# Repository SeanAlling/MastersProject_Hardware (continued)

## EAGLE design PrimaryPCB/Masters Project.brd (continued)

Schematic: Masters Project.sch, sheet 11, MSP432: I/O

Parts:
LED12: GREEN; CHIPLED_0603; PARTNO LG R971-KN-1
R24, R25: 10K; R0603; PARTNO RMCF0805JT10K0
R27: 1K; R0603; PARTNO RC0805JR-071KL
TP22, TP23, TP24, TP26, TP27, TP28, TP29, TP30: TPB1,27; B1,27
U12: MSP432P401R; LQFP100; PARTNO MSP432P401RIPZR

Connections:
!RTC_INT1: U12.22 (P2.6/PM_TA0.3); also elsewhere on the board
!RTC_INT2: U12.24 (P10.4/TA3.0/C0.7); also elsewhere on the board
CHARGE_STATUS: U12.32 (P3.0/PM_UCA2STE); also elsewhere on the board
DISPLAY_D/!C: TP27.TP, U12.36 (P3.4/PM_UCB2STE); also elsewhere on the board
FPGA_DONE: U12.23 (P2.7/PM_TA0.4); also elsewhere on the board
FRAM_WP: U12.4 (P1.0/UCA0STE); also elsewhere on the board
INTERRUPT_OPT3001: U12.5 (P1.1/UCA0CLK); also elsewhere on the board
MCU_EN_CTL3: U12.19 (P2.3/PM_UCA1TXD/PM_UCA1SIMO); also elsewhere on the board
MCU_EN_CTL4: U12.18 (P2.2/PM_UCA1RXD/PM_UCA1SOMI); also elsewhere on the board
MCU_EN_CTL5: U12.39 (P3.7/PM_UCB2SOMI/PM_UCB2SCL); also elsewhere on the board
MCU_EN_CTL6: U12.20 (P2.4/PM_TA0.1); also elsewhere on the board
MCU_FPGA_2: U12.71 (P5.7/TA2.2/VREF-/VEREF-/C1.6); also elsewhere on the board
MCU_FPGA_3: U12.70 (P5.6/TA2.1/VREF+/VEREF+/C1.7); also elsewhere on the board
MCU_FPGA_4: U12.69 (P5.5/A0); also elsewhere on the board
MCU_FPGA_5: U12.68 (P5.4/A1); also elsewhere on the board
MCU_FPGA_6: U12.67 (P5.3/A2); also elsewhere on the board
MCU_FPGA_7: U12.66 (P5.2/A3); also elsewhere on the board
MCU_FPGA_8: U12.65 (P5.1/A4); also elsewhere on the board
MCU_FPGA_9: U12.64 (P5.0/A5); also elsewhere on the board
MCU_FPGA_10: U12.63 (P4.7/A6); also elsewhere on the board
MCU_FPGA_11: U12.62 (P4.6/A7); also elsewhere on the board
MCU_FPGA_12: U12.61 (P4.5/A8); also elsewhere on the board
MCU_FPGA_13: U12.60 (P4.4/HSMCLK/SVMHOUT/A9); also elsewhere on the board
MCU_FPGA_14: U12.59 (P4.3/MCLK/RTCCLK/A10); also elsewhere on the board
MCU_FPGA_15: U12.58 (P4.2/ACLK/TA2CLK/A11); also elsewhere on the board
MCU_SCL: R25.1, TP29.TP, U12.11 (P1.7/UCB0SOMI/UCB0SCL); also elsewhere on the board
MCU_SDA: R24.1, TP30.TP, U12.10 (P1.6/UCB0SIMO/UCB0SDA); also elsewhere on the board
MCU_SD_HDC1080: U12.17 (P2.1/PM_UCA1CLK); also elsewhere on the board
MCU_SD_OPT3001: U12.16 (P2.0/PM_UCA1STE); also elsewhere on the board
unnamed: R27.2, U12.9 (P1.5/UCB0CLK)
unnamed: LED12.C, R27.1
P10.5: U12.25 (P10.5/TA3.1/C0.6); also elsewhere on the board
RTC_CLKOUT: U12.21 (P2.5/PM_TA0.2); also elsewhere on the board
SPI_CLK: TP24.TP, U12.33 (P3.1/PM_UCA2CLK); also elsewhere on the board
SPI_CS_DISPLAY: TP28.TP, U12.37 (P3.5/PM_UCB2CLK); also elsewhere on the board
SPI_CS_FPGA: U12.38 (P3.6/PM_UCB2SIMO/PM_UCB2SDA); also elsewhere on the board
SPI_MISO: U12.34 (P3.2/PM_UCA2RXD/PM_UCA2SOMI)
SPI_MOSI: TP26.TP, U12.35 (P3.3/PM_UCA2TXD/PM_UCA2SIMO); also elsewhere on the board
UART_RX_XBEE: TP23.TP, U12.6 (P1.2/UCA0RXD/UCA0SOMI); also elsewhere on the board
UART_TX_XBEE: TP22.TP, U12.7 (P1.3/UCA0TXD/UCA0SIMO); also elsewhere on the board
VCC_MCU: LED12.A, R24.2, R25.2; also elsewhere on the board

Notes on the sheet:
TEST POINTS
INPUTS
COMMUNICATION
OUTPUTS
I/O

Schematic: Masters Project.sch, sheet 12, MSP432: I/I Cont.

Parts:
JP3: 2X5_HEADER1.27MM; CORTEX_DEBUG_10PIN
TP31, TP32: TPB1,27; B1,27
U12: MSP432P401R; LQFP100; PARTNO MSP432P401RIPZR

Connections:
!FLASH_HOLD: U12.75 (P9.3/TA3.4); also elsewhere on the board
!FLASH_WP: U12.80 (P6.6/TA2.3/UCB3SIMO/UCB3SDA/C1.1); also elsewhere on the board
EINK_!RST: TP31.TP, U12.46 (P8.2/TA3.2/A23); also elsewhere on the board
EINK_BUSY: TP32.TP, U12.47 (P8.3/TA3CLK/A22); also elsewhere on the board
GND: JP3.2, JP3.4; also elsewhere on the board
MCU_FPGA_1: U12.74 (P9.2/TA3.3); also elsewhere on the board
MCU_SPI_CLK: U12.77 (P6.3/UCB1CLK/C1.4); also elsewhere on the board
MCU_SPI_CS: U12.76 (P6.2/UCB1STE/C1.5); also elsewhere on the board
MCU_SPI_MISO: U12.79 (P6.5/UCB1SOMI/UCB1SCL/C1.2); also elsewhere on the board
MCU_SPI_MOSI: U12.78 (P6.4/UCB1SIMO/UCB1SDA/C1.3); also elsewhere on the board
P7.5: JP3.9, U12.27 (P7.5/PM_TA1.3/C0.4)
P7.6: JP3.7, U12.28 (P7.6/PM_TA1.2/C0.3)
P7.7: JP3.5, U12.29 (P7.7/PM_TA1.1/C0.2)
P8.0: JP3.3, U12.30 (P8.0/UCB3STE/TA1.0/C0.1)
P8.1: JP3.1, U12.31 (P8.1/UCB3CLK/TA2.0/C0.0)
P10.5: JP3.6; also elsewhere on the board
VCC_MCU: JP3.8, JP3.10; also elsewhere on the board
XBEE_RESET: U12.26 (P7.4/PM_TA1.4/C0.5); also elsewhere on the board

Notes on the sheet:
External Pin Connections
TEST POINTS
INPUTS
OUTPUTS
I/O
COMMUNICATION

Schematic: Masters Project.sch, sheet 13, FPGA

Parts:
C37, C38, C42, C43, C46, C47, C50, C51, C54, C55: 0.1uF; C0603; PARTNO 08055C104KAT2A
JP1, JP4: 2X5_HEADER1.27MM; CORTEX_DEBUG_10PIN
R30, R31, R32: 5k; R0603; PARTNO RC0805FR-075K1L
R35: 2k; R0603; PARTNO RC0805FR-072KL
U1: LCMXO2-640HC-4TG100C-NEW; QFP50P1600X1600X160-100N

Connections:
FPGA_DONE: U1.76 (PT11D/DONE); also elsewhere on the board
GND: C37.2, C38.2, C42.2, C43.2, C46.2, C47.2, C50.2, C51.2, C54.2, C55.2, JP1.10, JP4.8, R35.1, U1.6 (GND), U1.22 (GND), U1.33 (GND), U1.44 (GND), U1.56 (GND), U1.72 (GND), U1.79 (GND), U1.92 (GND); also elsewhere on the board
MCU_FPGA_1: U1.28 (PB4B); also elsewhere on the board
MCU_FPGA_2: U1.29 (PB4C); also elsewhere on the board
MCU_FPGA_3: U1.30 (PB4D); also elsewhere on the board
MCU_FPGA_4: U1.31 (PB6A/MCLK/CCLK); also elsewhere on the board
MCU_FPGA_5: U1.32 (PB6B/SO/SPISO); also elsewhere on the board
MCU_FPGA_6: U1.34 (PB6C/PCLKT2_0); also elsewhere on the board
MCU_FPGA_7: U1.35 (PB6D/PCLKC2_0); also elsewhere on the board
MCU_FPGA_8: U1.36 (PB10A); also elsewhere on the board
MCU_FPGA_9: U1.37 (PB10B); also elsewhere on the board
MCU_FPGA_10: U1.38 (PB10C/PCLKT2_1); also elsewhere on the board
MCU_FPGA_11: U1.39 (PB10D/PCLKC2_1); also elsewhere on the board
MCU_FPGA_12: U1.40 (PB12A); also elsewhere on the board
MCU_FPGA_13: U1.41 (PB12B); also elsewhere on the board
MCU_FPGA_14: U1.42 (PB12C); also elsewhere on the board
MCU_FPGA_15: U1.43 (PB12D); also elsewhere on the board
PT9A: JP1.8, U1.88 (PT9A/PCLKT0_1)
PT9B: JP1.6, U1.87 (PT9B/PCLKC0_1)
PT9C: JP1.4, U1.86 (PT9C/SCL/PCLKT0_0)
PT9D: JP1.2, U1.85 (PT9D/SDA/PCLKC0_0)
PT10A: JP1.3, U1.84 (PT10A)
PT10B: JP1.5, U1.83 (PT10B)
PT10C: JP1.7, U1.82 (PT10C/JTAGENB)
PT10D: JP1.9, U1.81 (PT10D/PROGRAMN)
SPI_CS_FPGA: U1.48 (PB14C/SN); also elsewhere on the board
TCK: JP4.6, R35.2, U1.91 (PT7C/TCK)
TDI: JP4.5, R31.1, U1.94 (PT7B/TDI)
TDO: JP4.7, R30.1, U1.95 (PT7A/TDO)
TMS: JP4.3, R32.1, U1.90 (PT7D/TMS)
VCC_FPGA: C37.1, C38.1, C42.1, C43.1, C46.1, C47.1, C50.1, C51.1, C54.1, C55.1, JP1.1, JP4.1, R30.2, R31.2, R32.2, U1.5 (VCCIO3), U1.23 (VCCIO3), U1.26 (VCCIO2), U1.46 (VCCIO2), U1.50 (VCC), U1.55 (VCCIO1), U1.73 (VCCIO1), U1.80 (VCCIO0), U1.93 (VCCIO0), U1.100 (VCC); also elsewhere on the board

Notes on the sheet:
Decoupling capacitors
JTAG Programmer
POWER
MCU-FPGA Connections
VCCIO1
VCCIO2
VCCIO3
VCCIO0
INPUTS
OUTPUTS
COMMUNICATION
I/O Connections
External Header
NOTE: Place close to indicated voltage pins.
UNUSED

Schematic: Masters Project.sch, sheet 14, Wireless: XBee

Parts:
C57: 47uF; C0603; PARTNO GRM21BR61A476ME15L
JP2: 1X3_HEADER; 1X3_FEMALE_HEADER_THROUGH_HOLE; PARTNO PRPC040SAAN-RC
JP26: XBEE-1B1; XBEE-1; PARTNO NPPN101BFCN-RC
LED14, LED15, LED18: GREEN; CHIPLED_0603; PARTNO LG R971-KN-1
LED16, LED17: GREEN; SML0805; PARTNO LG R971-KN-1
R37, R38, R39, R40, R41: 1K; R0603; PARTNO RC0805JR-071KL

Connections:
ASSOCIATE_LED: JP26.15 (DIO5), R39.1
GND: C57.2, JP26.10 (GND), LED16.C, LED17.C, LED18.C; also elsewhere on the board
unnamed: LED15.C, R38.2
unnamed: LED14.C, R37.2
unnamed: LED16.A, R39.2
unnamed: LED18.A, R41.2
unnamed: LED17.A, R40.2
RSSI: JP26.6 (RSSI), R41.1
STATUS_LED: JP26.13 (DIO9), R40.1
UART_RX_XBEE: JP26.2 (DOUT), R37.1; also elsewhere on the board
UART_TX_XBEE: JP26.3 (DIN), R38.1; also elsewhere on the board
VCC_XBEE: C57.1, JP26.1 (VDD), LED14.A, LED15.A; also elsewhere on the board
XBEE_CTS: JP2.2, JP26.12 (CTS)
XBEE_DTR: JP2.3, JP26.9 (DTR)
XBEE_RESET: JP26.5 (RESET); also elsewhere on the board
XBEE_RTS: JP2.1, JP26.16 (RTS)

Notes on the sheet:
NOTE: This module can be swapped for any module that is pn compattble with Xbee. For example the WiFi or RF modules by digi can be placed here.
NOTE: Minimum connections: VCC, GND, DOUT & DIN
NOTE: Do not populate for reduced current
Decoupling Capacitors
Status LED's
XBee
NOTE: Populate J2 only if XBee upgrades are needed
XBee Update
NOTE: Use to update software on XBee SOC
NOTE: Minimum connections for updating firmware: VCC, GND, DIN, DOUT, RTS & DTR
INPUTS
COMMUNICATION

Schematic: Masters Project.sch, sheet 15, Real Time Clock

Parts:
C68: 11mF; C1210K
Q9: ABS07-LR; 2-SMD
R3: 1K; R0603
TP40, TP41, TP42: TPB1,27; B1,27
U16: PCF8523; TSSOP14

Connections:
!RTC_INT1: TP40.TP, U16.13 (!INT1); also elsewhere on the board
!RTC_INT2: TP42.TP, U16.7 (!INT2); also elsewhere on the board
+BAT: R3.2, U16.4 (VBAT), U16.14 (VDD); also elsewhere on the board
GND: C68.2, U16.5 (VSS); also elsewhere on the board
MCU_SCL: U16.11 (SCL); also elsewhere on the board
MCU_SDA: U16.10 (SDA); also elsewhere on the board
unnamed: Q9.2, U16.1 (OSCI)
unnamed: Q9.1, U16.2 (OSCO)
RTC_CLKOUT: TP41.TP, U16.8 (CLKOUT); also elsewhere on the board
RTC_VCAP: C68.1, R3.1

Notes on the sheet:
SuperCap
NOTE: Resistor used to provide current limiting to the capacitor. Larger resistor = longer RC time constant = longer time to charge
Real Time Clock
NOTE: At ambiant temperature the average supply is 150nA. The maximum supply current is 3.6uA.
TEST POINTS
INPUTS
COMMUNICATION
OUTPUTS

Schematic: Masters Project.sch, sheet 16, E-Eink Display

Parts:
C1, C2, C36, C39, C40, C41, C44, C45, C48, C49, C52: 1uF; C0603
D1, D3, D4: SCHOTTKY; SOD3716X128
L2: 100uH; LPS3015
Q3: MOSFET-NCH; SOT95P237X112-3
R1: 0.47; R0603
R2: 100k; R0603
U18: 4.2-E-INK-DISPLAY; FPC-24PIN-0.5MM

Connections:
DISPLAY_D/!C: U18.11 (D/!C); also elsewhere on the board
EINK_!RST: U18.10 (!RST); also elsewhere on the board
EINK_BUSY: U18.9 (BUSY); also elsewhere on the board
GDR: Q3.1 (G), R2.2, U18.2 (GDR)
GND: C1.2, C2.2, C36.2, C39.2, C40.2, C41.2, C44.2, C45.2, C48.2, C49.2, D4.2 (C), R1.1, R2.1, U18.8 (BS1), U18.17 (VSS); also elsewhere on the board
PREVGH: C48.1, D1.2 (C), U18.21 (PREVGH)
PREVGL: C49.1, D3.1 (A), U18.23 (PREVGL)
RESE: Q3.2 (S), R1.2, U18.3 (RESE)
SPI_CLK: U18.13 (D0(SCK)); also elsewhere on the board
SPI_CS_DISPLAY: U18.12 (!CS); also elsewhere on the board
SPI_MOSI: U18.14 (D1(MOSI)); also elsewhere on the board
SW: C52.1, D1.1 (A), L2.1, Q3.3 (D)
SWGL: C52.2, D3.2 (C), D4.1 (A)
VCC_DISPLAY: C41.1, L2.2, U18.15 (VDDIO), U18.16 (VCI); also elsewhere on the board
VCOM: C40.1, U18.24 (VCOM)
VDD: C1.1, U18.18 (VDD)
VGH: C45.1, U18.5 (VGH)
VGL: C44.1, U18.4 (VGL)
VPP: C2.1, U18.19 (VPP)
VSH: C36.1, U18.20 (VSH)
VSL: C39.1, U18.22 (VSL)

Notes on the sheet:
RATED >= 25V
RATED>= 50V
RATED >=50V
Power Converter
INPUTS
COMMUNICATION
OUTPUTS

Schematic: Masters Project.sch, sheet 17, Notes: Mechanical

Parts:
FD1, FD2, FD3, FD4, FD5, FD6, FD7, FD8: FIDUCIAL1X2; FIDUCIAL-1X2
H1, H2, H3, H4: STAND-OFF

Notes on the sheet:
Fiducial One per corner, top and bottom
Mounting Hole One per corner
BOTTOM
TOP
GND
Stackup

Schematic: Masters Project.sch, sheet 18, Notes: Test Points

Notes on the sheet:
TP1: +BAT TP2: GND TP3: VCC_USB TP4: VCC_HDC1080 TP5: VCC_OPT3001 TP6: VCC_FPGA TP7: VCC_XBEE TP8: VCC_MEMORY TP9: VCC_DISPLAY TP10: VCC_MCU TP11: GND TP12: GND TP13: GND TP14: GND TP15: GND TP16: GND TP17: GND TP18: GND TP19: !RST TP20: N$139
TP21: N$131 TP22: UART_TX_XBEE TP23: UART_RX_XBEE TP24: SPI_CLK TP25: CHARGE_STATUS TP26: SPI_MOSI TP27: DISPLAY_D/!C TP28: SPI_CS_DISPLAY TP29: MCU_SCL TP30: MCU_SDA TP31: EINK_!RST TP32: EINK_BUSY TP33: !FLASH_WP TP34: FRAM_WP TP35: !FLASH_HOLD TP36: MCU_SPI_MISO TP37: MCU_SPI_CS TP38: MCU_SPI_CL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

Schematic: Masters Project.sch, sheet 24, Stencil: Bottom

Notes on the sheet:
N/A

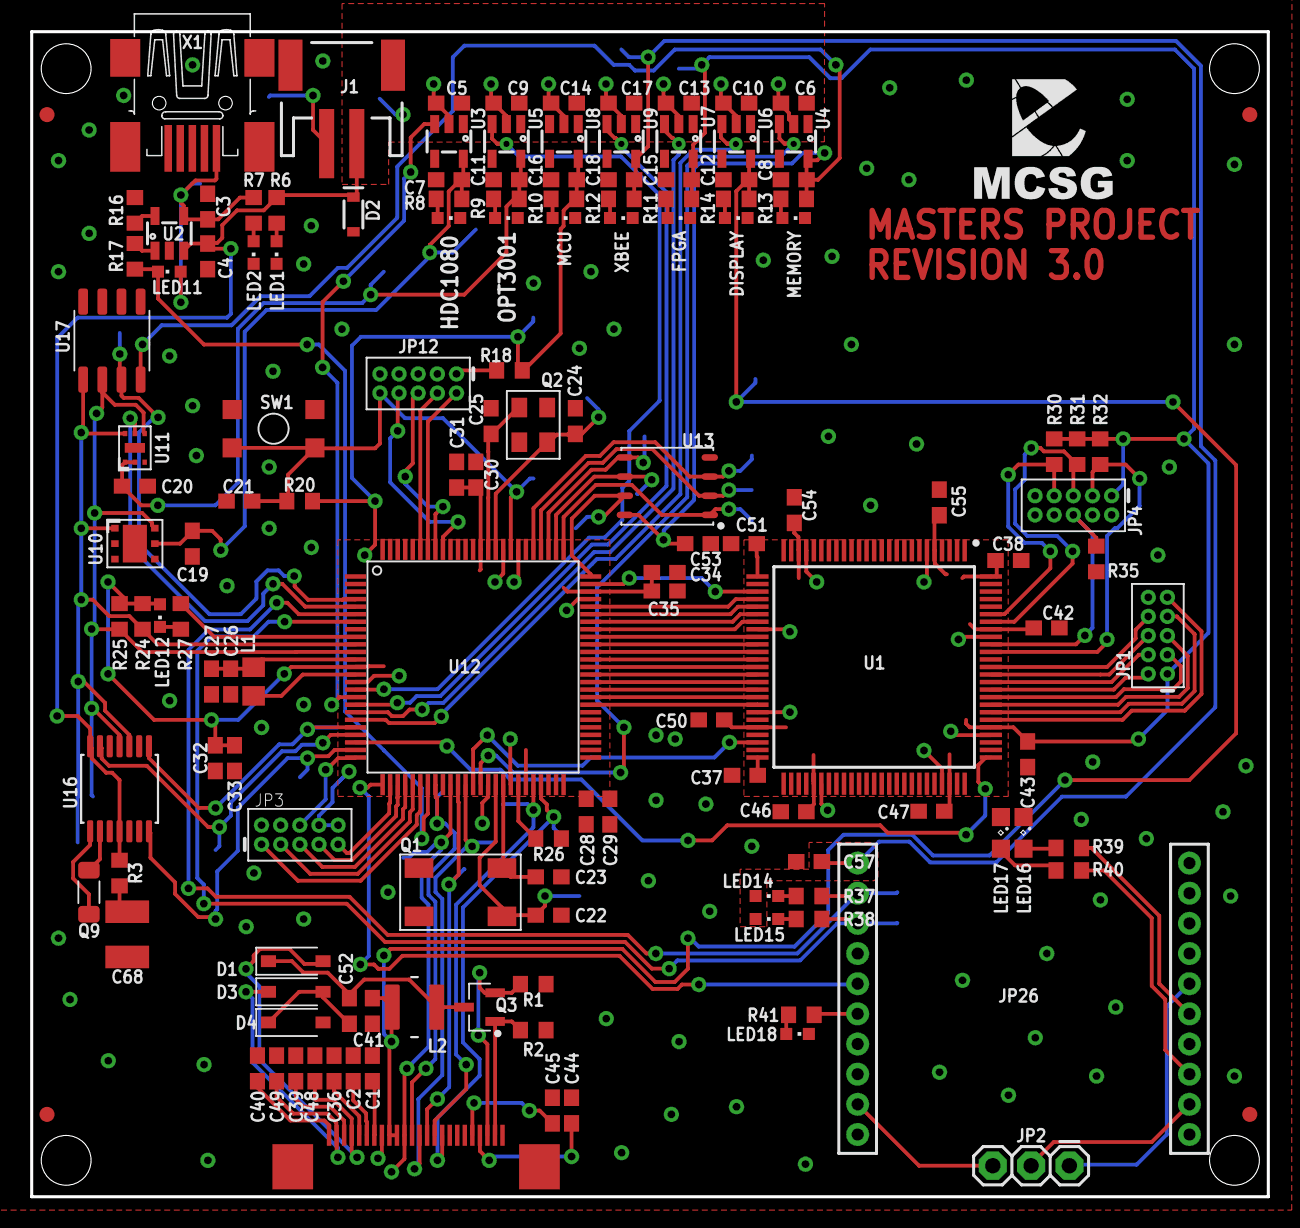
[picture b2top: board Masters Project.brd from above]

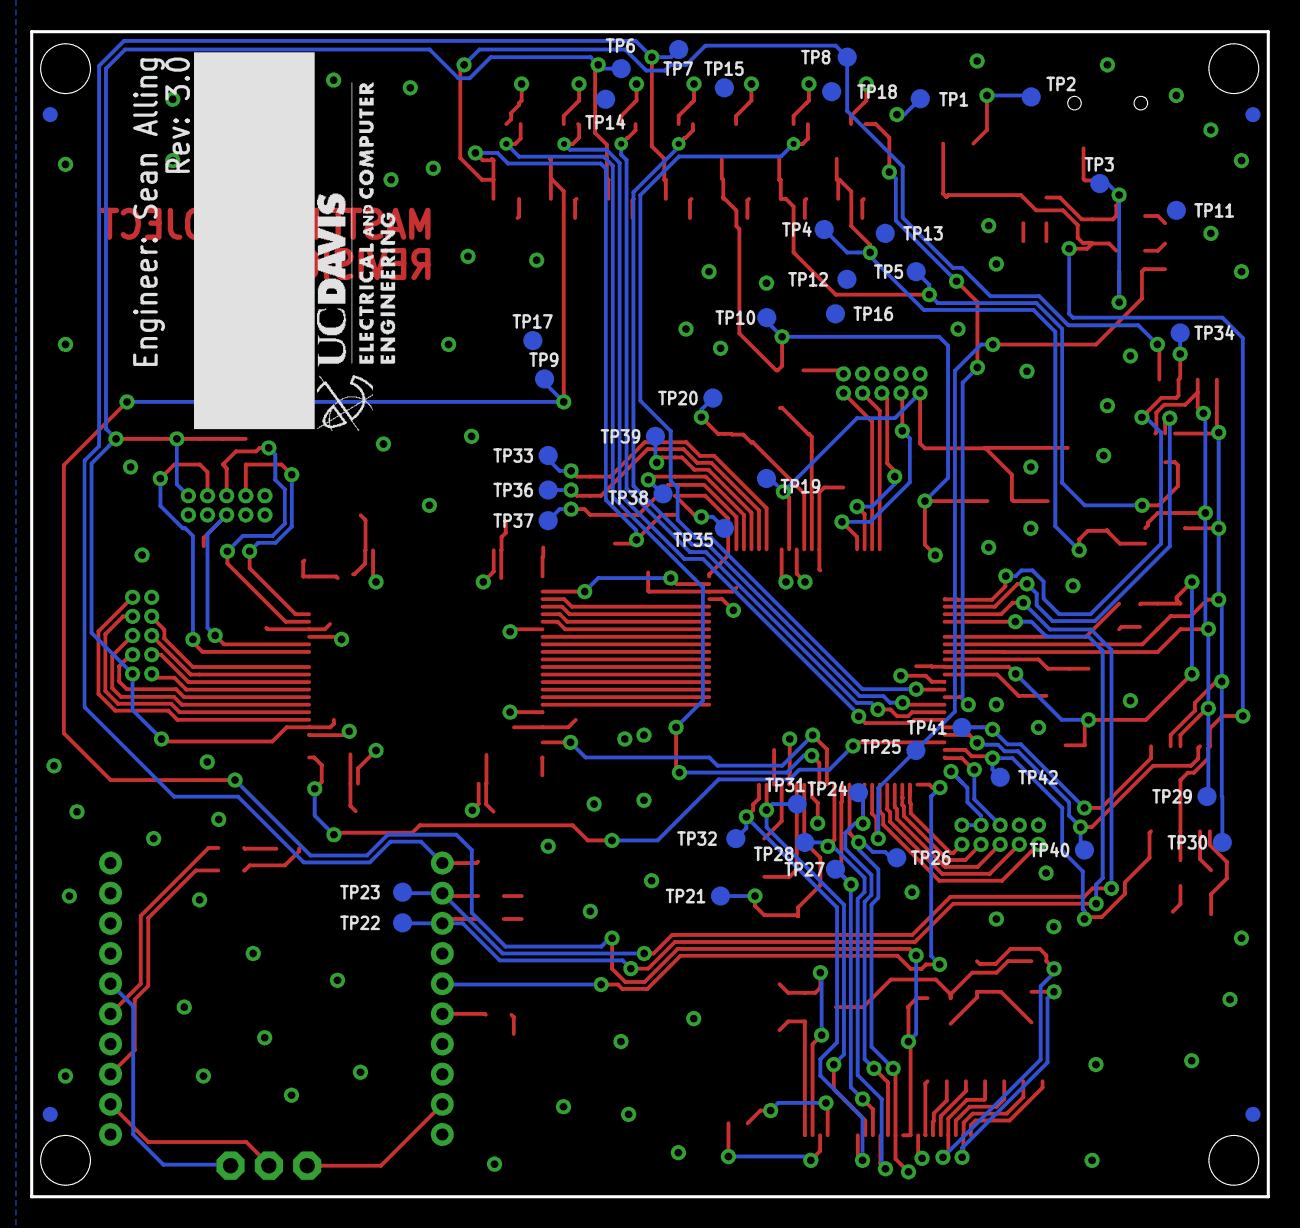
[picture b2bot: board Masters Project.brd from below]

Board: 2 copper layers, 82.0 x 77.3 mm, 194 parts (47 on the bottom side), 127 nets.

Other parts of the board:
U$1: UC_DAVIS_EE_1.00_INCH
U$2: UC_DAVIS_ENG
U$3: MCSG_SMALL

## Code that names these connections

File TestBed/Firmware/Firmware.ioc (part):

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PA6.Mode=IN3-Single-Ended
Mcu.UserName=STM32G431C6Tx
PB10.Mode=Asynchronous
PA11.Mode=Device
PB11.Signal=USART3_RX
PB13.Signal=SPI2_SCK
PB15.Signal=SPI2_MOSI
RCC.SYSCLKSource=RCC_SYSCLKSOURCE_PLLCLK
PA12.Signal=USB_DP
PA4.Mode=IN17-Single-Ended
PB6.Signal=GPIO_Input
RCC.HSE_VALUE=8000000
PB3.Mode=Asynchronous
PA15.Mode=Asynchronous
PA14.Mode=Serial_Wire
PB14.Mode=Full_Duplex_Master
PA0.Mode=IN1-Single-Ended
PB7.Signal=I2C1_SDA
PA8.Signal=S_TIM1_CH1
PA0.Signal=ADC1_IN1
Mcu.Package=LQFP48
PB1.Signal=GPIO_Input
PA6.Signal=ADC2_IN3
PA10.Signal=S_TIM1_CH3
PA15.Signal=USART2_RX
PB13.Mode=Full_Duplex_Master
PA3.Signal=ADC1_IN4
PA5.Mode=IN13-Single-Ended
PB8-BOOT0.Mode=I2C
PA7.Mode=IN4-Single-Ended
PA13.Signal=SYS_JTMS-SWDIO
PA3.Mode=IN4-Single-Ended
PB11.Mode=Asynchronous
PA9.Signal=S_TIM1_CH2
PA1.Signal=ADC1_IN2
PB10.Signal=USART3_TX
PB14.Signal=SPI2_MISO
PA5.Signal=ADC2_IN13
PB0.Mode=IN15-Single-Ended
PB8-BOOT0.Signal=I2C1_SCL
board=custom
PB15.Mode=Full_Duplex_Master
PA1.Mode=IN2-Single-Ended
PA13.Mode=Serial_Wire
Mcu.Name=STM32G431C(6-8-B)Tx
PA2.Signal=ADC1_IN3
PB3.Signal=USART2_TX
PA4.Signal=ADC2_IN17
RCC.SYSCLKFreq_VALUE=170000000
PA12.Mode=Device
PB7.Mode=I2C
PA11.Signal=USB_DM
PA14.Signal=SYS_JTCK-SWCLK
PA2.Mode=IN3-Single-Ended
PB0.Signal=ADC1_IN15
PB12.Signal=GPIO_Output
PA7.Signal=ADC2_IN4

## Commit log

2020-08-21 Added DOI to README
